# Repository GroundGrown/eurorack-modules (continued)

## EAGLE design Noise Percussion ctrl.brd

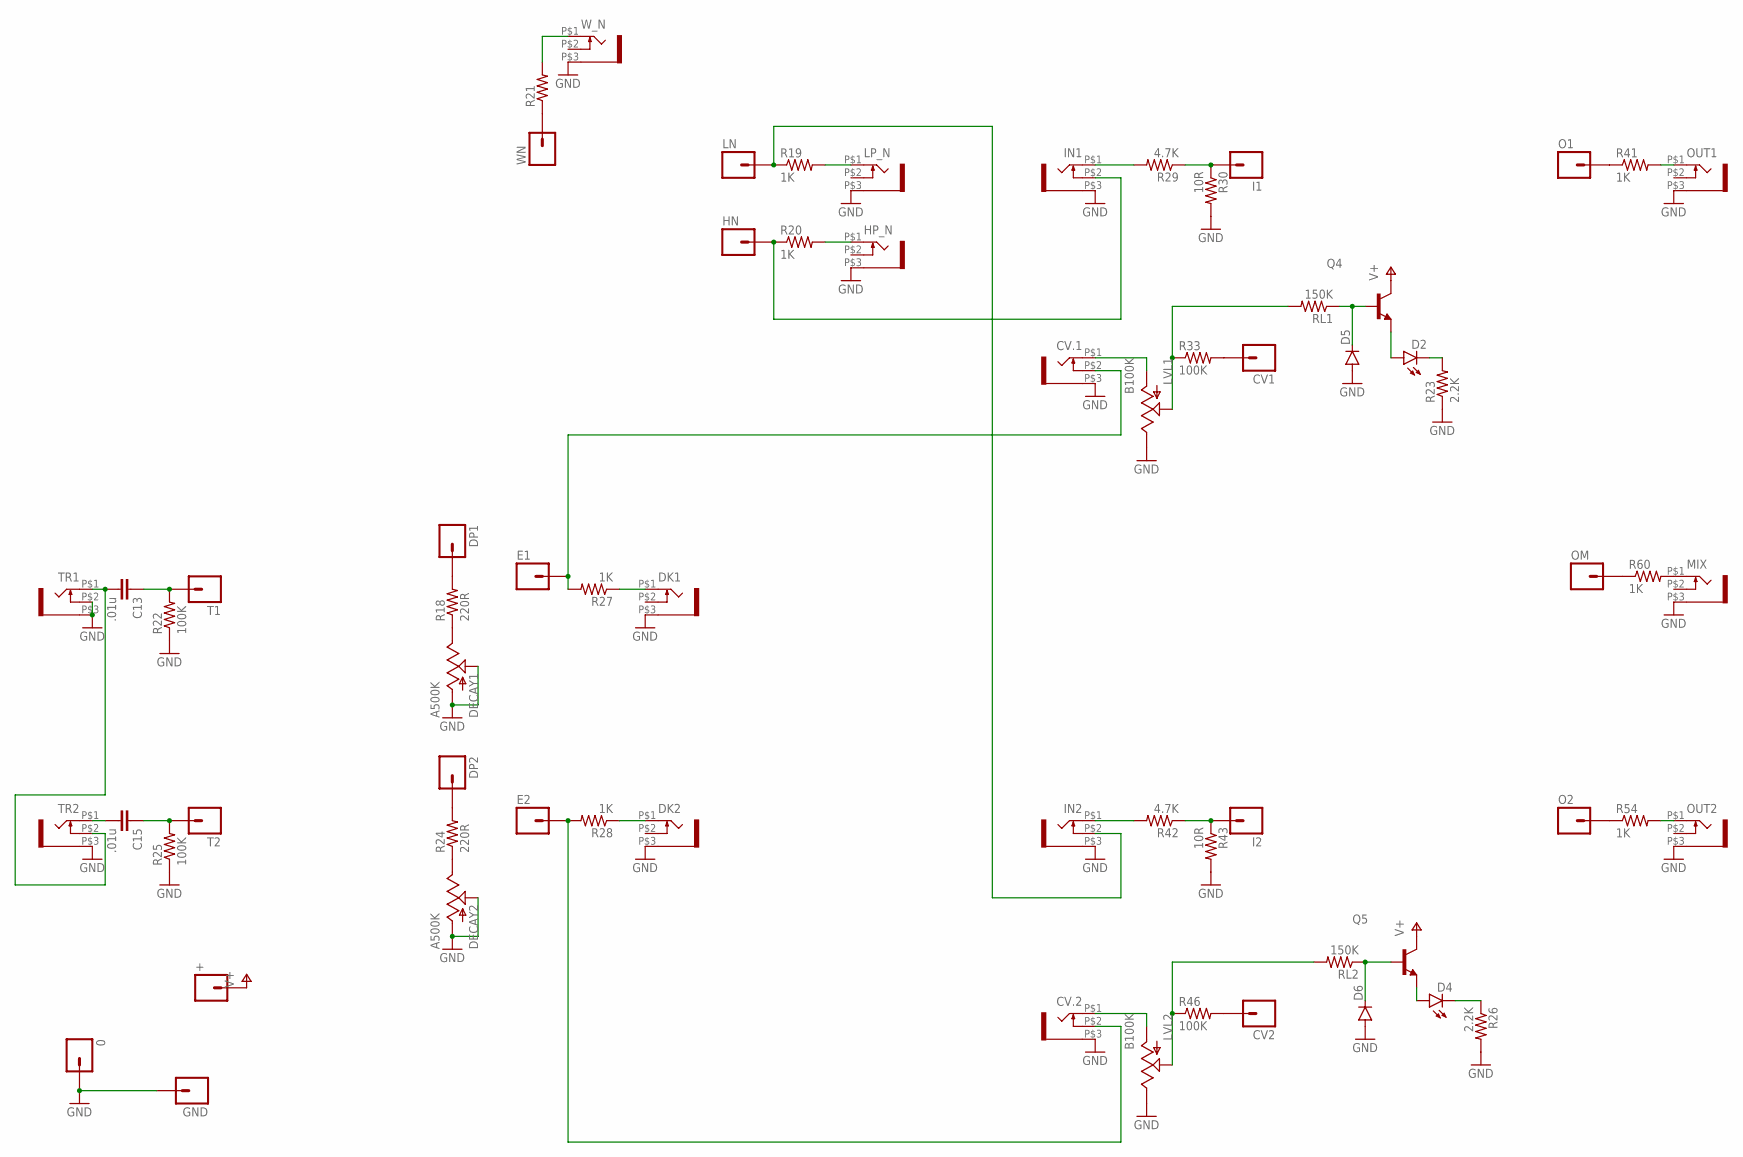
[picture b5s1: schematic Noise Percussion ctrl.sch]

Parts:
0: M01PTH; 1X01
+: M01PTH; 1X01
C13, C15: .01u; 0805
CV1, CV2: M01PTH; 1X01
CV.1, CV.2: WQP-PJ301M-12_JACK
D2, D4: LED3MM
D5, D6: DIODESOD123; SOD-123
DECAY1, DECAY2: A500K; ALPS_POT
DK1, DK2: WQP-PJ301M-12_JACK
DP1, DP2: M01PTH; 1X01
E1, E2: M01PTH; 1X01
GND: M01PTH; 1X01
HN: M01PTH; 1X01
HP_N: WQP-PJ301M-12_JACK
I1, I2: M01PTH; 1X01
IN1, IN2: WQP-PJ301M-12_JACK
LN: M01PTH; 1X01
LP_N: WQP-PJ301M-12_JACK
LVL1, LVL2: B100K; ALPS_POT
MIX: WQP-PJ301M-12_JACK
O1, O2: M01PTH; 1X01
OM: M01PTH; 1X01
OUT1, OUT2: WQP-PJ301M-12_JACK
Q4, Q5: MMBT3904LT1-NPN-SOT23-BEC; SOT23-BEC
R18, R24: 220R; 0805
R19, R20, R27, R28, R41, R54, R60: 1K; 0805
R21: RESISTOR0805-RES; 0805
R22, R25, R33, R46: 100K; 0805
R23, R26: 2.2K; 0805
R29, R42: 4.7K; 0805
R30, R43: 10R; 0805
RL1, RL2: 150K; 0805
T1, T2: M01PTH; 1X01
TR1, TR2: WQP-PJ301M-12_JACK
WN: M01PTH; 1X01
W_N: WQP-PJ301M-12_JACK

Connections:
GND: 0.1, CV.1.P$3 (1), CV.2.P$3 (1), D5.A, D6.A, DECAY1.P$2 (S), DECAY1.P$3 (A), DECAY2.P$2 (S), DECAY2.P$3 (A), DK1.P$3 (1), DK2.P$3 (1), GND.1, HP_N.P$3 (1), IN1.P$3 (1), IN2.P$3 (1), LP_N.P$3 (1), LVL1.P$1 (E), LVL2.P$1 (E), MIX.P$3 (1), OUT1.P$3 (1), OUT2.P$3 (1), R22.1, R23.1, R25.1, R26.2, R30.2, R43.2, TR1.P$2 (3), TR1.P$3 (1), TR2.P$3 (1), W_N.P$3 (1)
unnamed: D6.C, Q5.B, RL2.1
unnamed: HN.1, IN1.P$2 (3), R20.1
unnamed: IN1.P$1 (2), R29.2
unnamed: I1.1, R29.1, R30.1
unnamed: IN2.P$2 (3), LN.1, R19.1
unnamed: D5.C, Q4.B, RL1.1
unnamed: R21.1, WN.1
unnamed: CV.1.P$2 (3), E1.1, R27.2
unnamed: CV.2.P$2 (3), E2.1, R28.2
unnamed: DP1.1, R18.2
unnamed: DP2.1, R24.2
unnamed: O1.1, R41.1
unnamed: OM.1, R60.1
unnamed: DK2.P$1 (2), R28.1
unnamed: O2.1, R54.1
unnamed: CV1.1, R33.2
unnamed: CV2.1, R46.2
unnamed: D2.A, Q4.E
unnamed: D2.K (C), R23.2
unnamed: R21.2, W_N.P$1 (2)
unnamed: LP_N.P$1 (2), R19.2
unnamed: D4.A, Q5.E
unnamed: D4.K (C), R26.1
unnamed: HP_N.P$1 (2), R20.2
unnamed: C13.2, TR1.P$1 (2), TR2.P$2 (3)
unnamed: C13.1, R22.2, T1.1
unnamed: DECAY1.P$1 (E), R18.1
unnamed: C15.2, TR2.P$1 (2)
unnamed: C15.1, R25.2, T2.1
unnamed: DECAY2.P$1 (E), R24.1
unnamed: DK1.P$1 (2), R27.1
unnamed: CV.1.P$1 (2), LVL1.P$3 (A)
unnamed: LVL1.P$2 (S), R33.1, RL1.2
unnamed: OUT1.P$1 (2), R41.2
unnamed: IN2.P$1 (2), R42.2
unnamed: I2.1, R42.1, R43.1
unnamed: CV.2.P$1 (2), LVL2.P$3 (A)
unnamed: LVL2.P$2 (S), R46.1, RL2.2
unnamed: OUT2.P$1 (2), R54.2
unnamed: MIX.P$1 (2), R60.2
V+: +.1, Q4.C, Q5.C

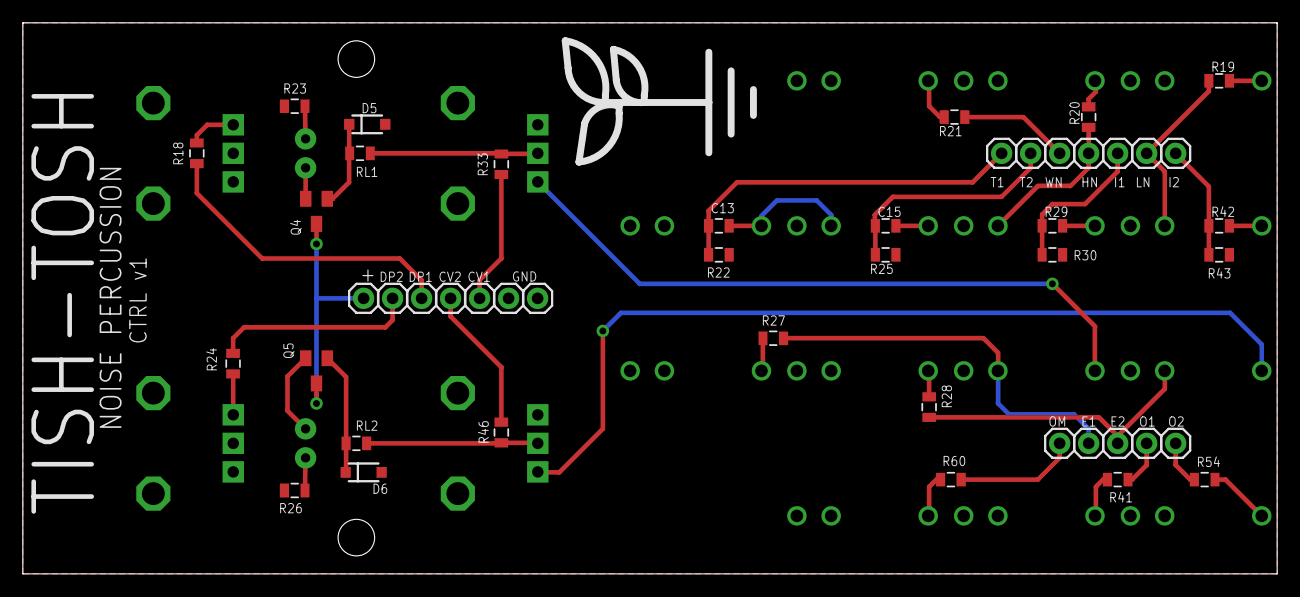
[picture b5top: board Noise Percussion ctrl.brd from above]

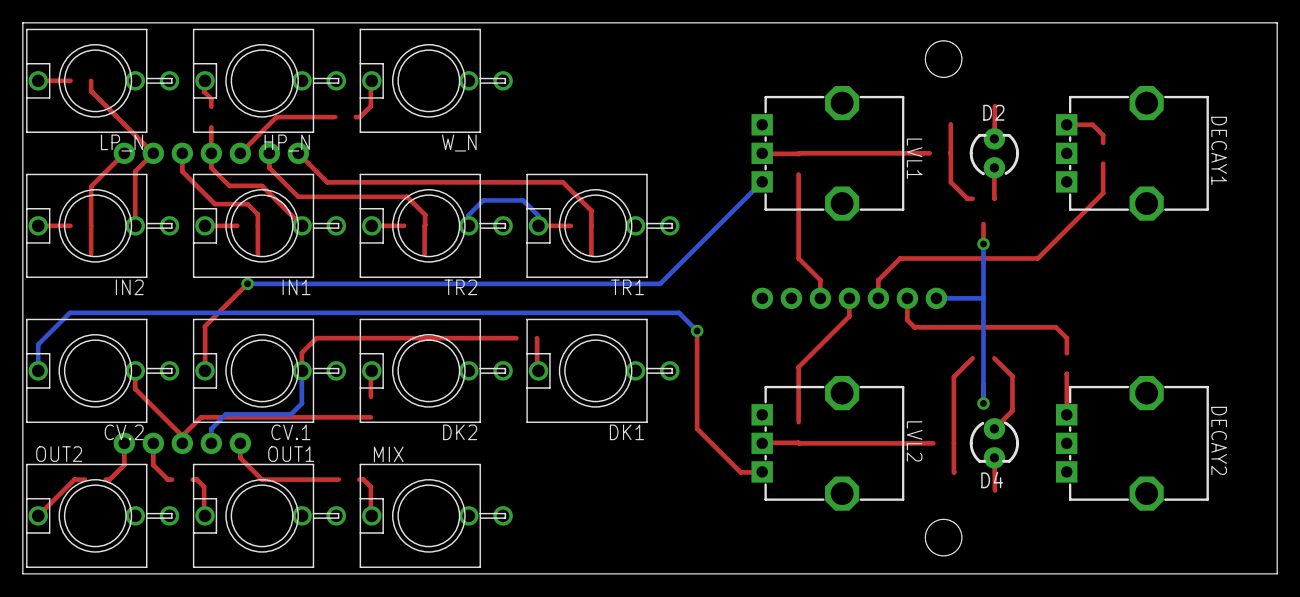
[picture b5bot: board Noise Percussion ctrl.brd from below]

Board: 2 copper layers, 109.9 x 48.3 mm, 68 parts (20 on the bottom side), 42 nets.

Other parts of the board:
U$1: LOGO_LARGE

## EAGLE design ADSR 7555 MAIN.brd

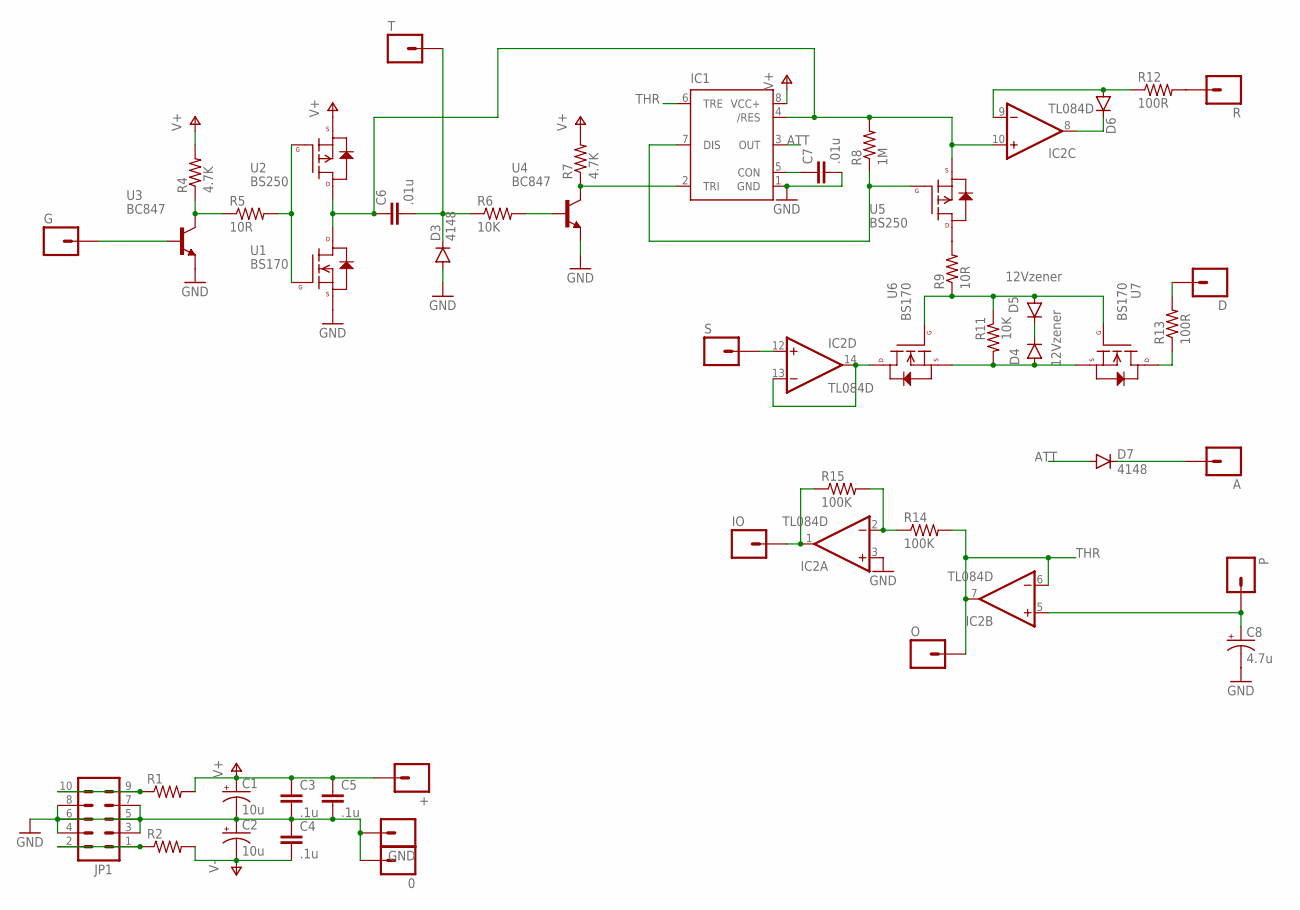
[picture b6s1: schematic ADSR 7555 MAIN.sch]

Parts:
0: M01PTH; 1X01
+: M01PTH; 1X01
A: M01PTH; 1X01
C1, C2: 10u; CPOL-RADIAL-10UF-25V
C3, C4, C5: .1u; 0805
C6, C7: .01u; 0805
C8: 4.7u; CPOL-RADIAL-10UF-25V
D: M01PTH; 1X01
D3, D7: 4148; SOD-123
D4, D5: 12Vzener; SOD-123
D6: DIODESOD123; SOD-123
G: M01PTH; 1X01
GND: M01PTH; 1X01
IC1: NE555D; SO08
IC2: TL084D; SO14
IO: M01PTH; 1X01
JP1: M05X2PTH; AVR_ICSP
O: M01PTH; 1X01
P: M01PTH; 1X01
R: M01PTH; 1X01
R1, R2: RESISTOR0805-RES; 0805@1
R4, R7: 4.7K; 0805@1
R5, R9: 10R; 0805@1
R6, R11: 10K; 0805@1
R8: 1M; 0805@1
R12, R13: 100R; 0805@1
R14, R15: 100K; 0805@1
S: M01PTH; 1X01
T: M01PTH; 1X01
U1, U6, U7: BS170; SOT23-3
U2, U5: BS250; SOT23-3
U3, U4: BC847; SOT23

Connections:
ATT: D7.A, IC1.3 (OUT)
GND: 0.1, C1.2 (-), C2.1 (+), C3.2, C4.1, C5.2, C7.2, C8.2 (-), D3.A, GND.1, IC1.1 (GND), IC2.3 (+IN), JP1.3, JP1.4, JP1.5, JP1.6, JP1.7, JP1.8, U1.2 (S), U3.2 (E), U4.2 (E)
unnamed: JP1.9, JP1.10, R1.1
unnamed: JP1.1, JP1.2, R2.1
unnamed: IC1.2 (TRI), R7.1, U4.3 (C)
unnamed: G.1, U3.1 (B)
unnamed: C8.1 (+), IC2.5 (+IN), P.1
unnamed: R4.1, R5.1, U3.3 (C)
unnamed: C7.1, IC1.5 (CON)
unnamed: R5.2, U1.1 (G), U2.1 (G)
unnamed: C6.1, IC1.4 (/RES), IC2.10 (+IN), R8.2, U1.3 (D), U2.3 (D), U5.2 (S)
unnamed: C6.2, D3.C, R6.1, T.1
unnamed: R6.2, U4.1 (B)
unnamed: R.1, R12.2
unnamed: IC1.7 (DIS), R8.1, U5.1 (G)
unnamed: R9.2, U5.3 (D)
unnamed: D6.A, IC2.9 (-IN), R12.1
unnamed: IC2.12 (+IN), S.1
unnamed: IC2.13 (-IN), IC2.14 (OUT), U6.3 (D)
unnamed: D4.A, R11.2, U6.2 (S), U7.2 (S)
unnamed: D4.C, D5.C
unnamed: D5.A, R9.1, R11.1, U6.1 (G), U7.1 (G)
unnamed: A.1, D7.C
unnamed: D6.C, IC2.8 (OUT)
unnamed: D.1, R13.2
unnamed: R13.1, U7.3 (D)
unnamed: IC2.2 (-IN), R14.1, R15.2
unnamed: IC2.1 (OUT), IO.1, R15.1
THR: IC1.6 (TRE), IC2.6 (-IN), IC2.7 (OUT), O.1, R14.2
V+: +.1, C1.1 (+), C3.1, C5.1, IC1.8 (VCC+), IC2.4 (V+), R1.2, R4.2, R7.2, U2.2 (S)
V-: C2.2 (-), C4.2, IC2.11 (V-), R2.2

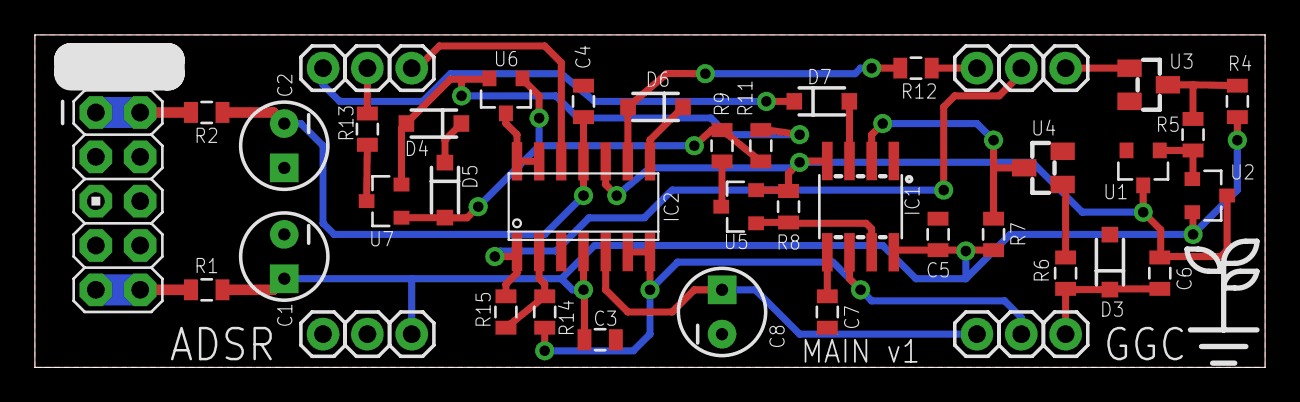
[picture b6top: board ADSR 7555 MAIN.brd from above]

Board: 2 copper layers, 70.5 x 19.1 mm, 49 parts (0 on the bottom side), 31 nets.

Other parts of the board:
U$1: LOGO_SMALL

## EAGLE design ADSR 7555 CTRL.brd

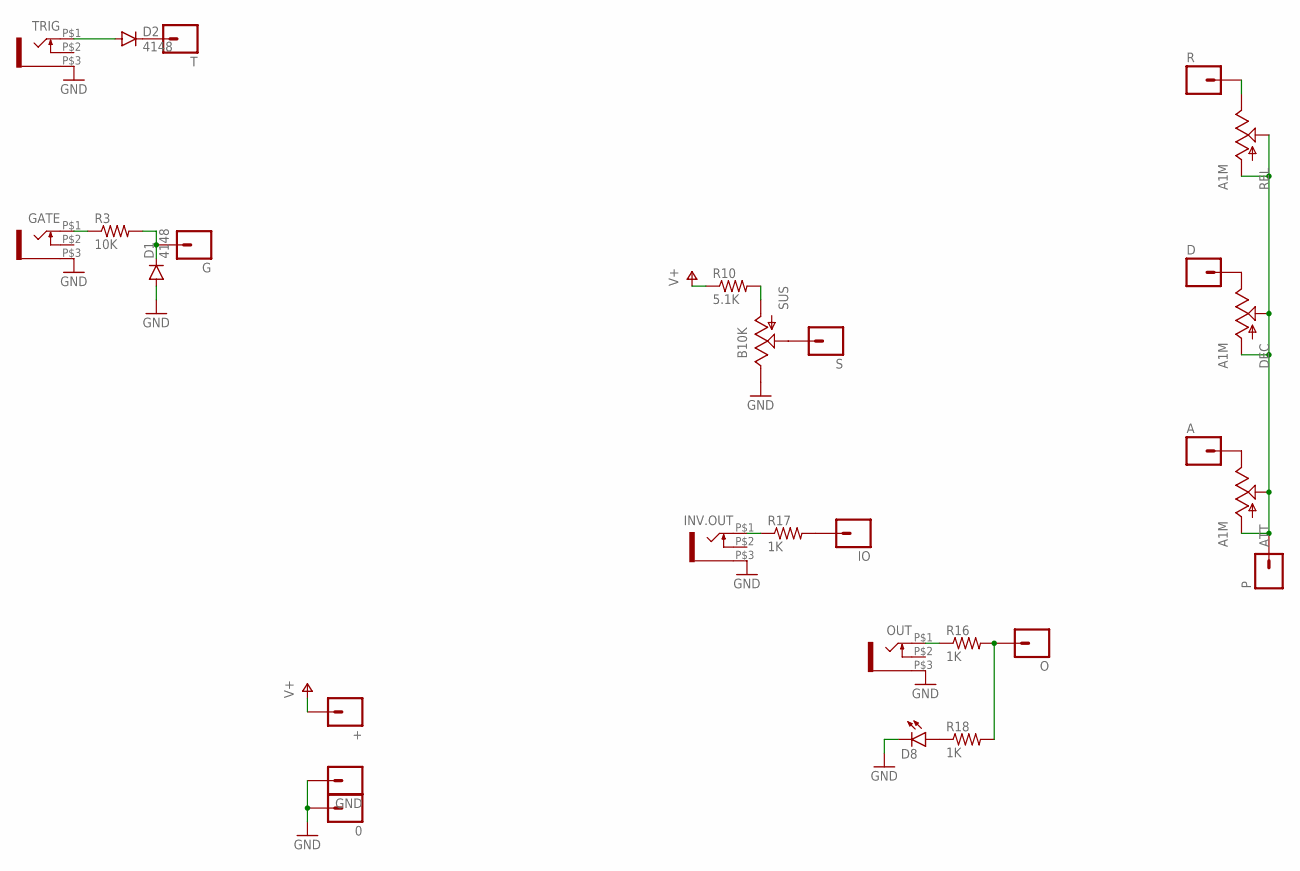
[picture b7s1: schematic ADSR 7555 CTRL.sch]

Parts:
0: M01PTH; 1X01
+: M01PTH; 1X01
A: M01PTH; 1X01
ATT: A1M; ALPS_POT
D: M01PTH; 1X01
D1, D2: 4148; SOD-123
D8: LED3MM
DEC: A1M; ALPS_POT
G: M01PTH; 1X01
GATE: WQP-PJ301M-12_JACK
GND: M01PTH; 1X01
INV.OUT: WQP-PJ301M-12_JACK
IO: M01PTH; 1X01
O: M01PTH; 1X01
OUT: WQP-PJ301M-12_JACK
P: M01PTH; 1X01
R: M01PTH; 1X01
R3: 10K; 0805@1
R10: 5.1K; 0805@1
R16, R17, R18: 1K; 0805@1
REL: A1M; ALPS_POT
S: M01PTH; 1X01
SUS: B10K; ALPS_POT
T: M01PTH; 1X01
TRIG: WQP-PJ301M-12_JACK

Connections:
GND: 0.1, D1.A, D8.K (C), GATE.P$3 (1), GND.1, INV.OUT.P$3 (1), OUT.P$3 (1), SUS.P$1 (E), TRIG.P$3 (1)
unnamed: D2.C, T.1
unnamed: S.1, SUS.P$2 (S)
unnamed: IO.1, R17.2
unnamed: GATE.P$1 (2), R3.1
unnamed: D1.C, G.1, R3.2
unnamed: O.1, R16.2, R18.2
unnamed: A.1, ATT.P$1 (E)
unnamed: D.1, DEC.P$1 (E)
unnamed: D8.A, R18.1
unnamed: D2.A, TRIG.P$1 (2)
unnamed: R10.2, SUS.P$3 (A)
unnamed: R.1, REL.P$1 (E)
unnamed: ATT.P$2 (S), ATT.P$3 (A), DEC.P$2 (S), DEC.P$3 (A), P.1, REL.P$2 (S), REL.P$3 (A)
unnamed: INV.OUT.P$1 (2), R17.1
unnamed: OUT.P$1 (2), R16.1
V+: +.1, R10.1

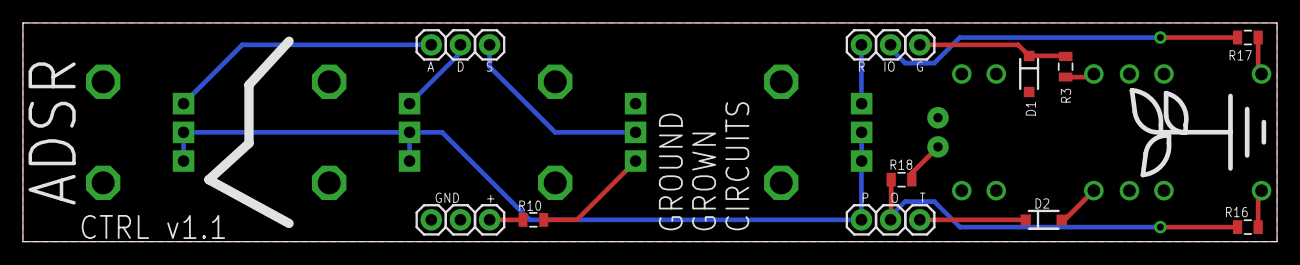
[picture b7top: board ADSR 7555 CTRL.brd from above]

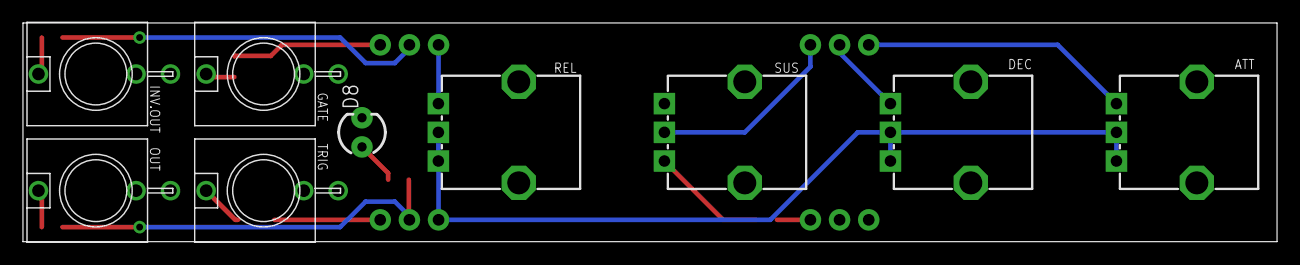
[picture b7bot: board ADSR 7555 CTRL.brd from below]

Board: 2 copper layers, 109.2 x 19.1 mm, 29 parts (9 on the bottom side), 17 nets.

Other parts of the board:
U$1: LOGO_MED

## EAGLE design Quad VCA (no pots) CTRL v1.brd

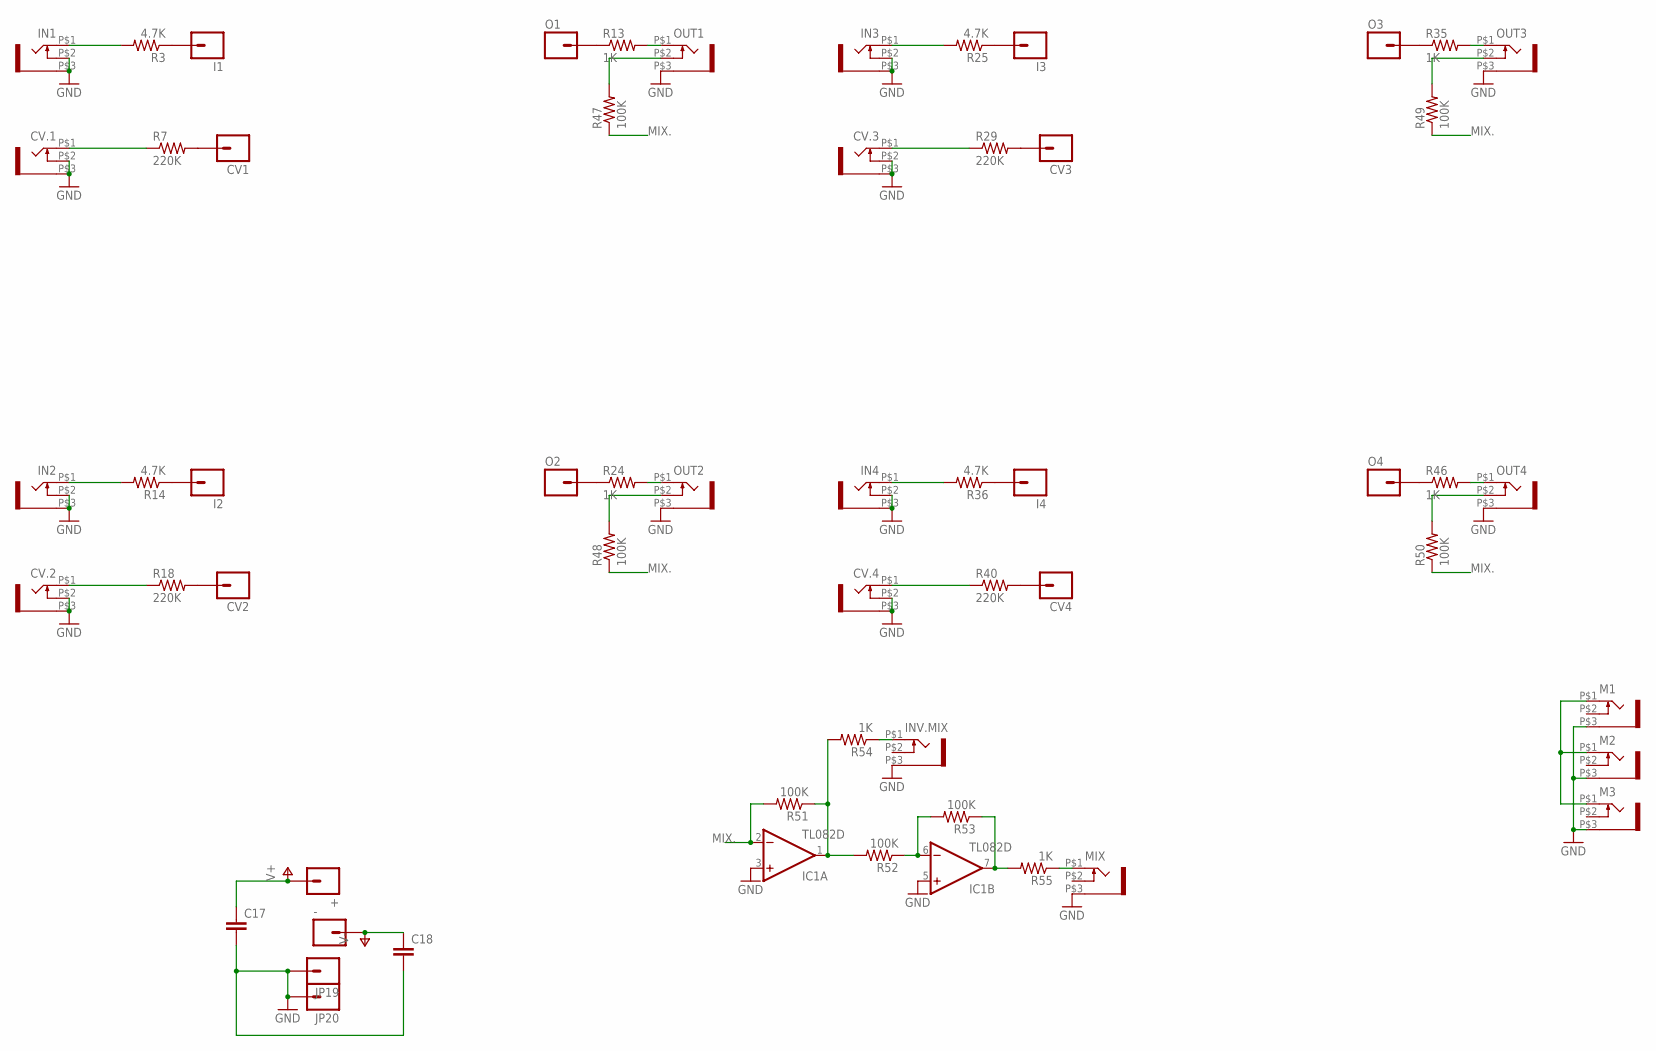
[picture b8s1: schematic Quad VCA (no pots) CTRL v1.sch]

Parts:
+: M01PTH; 1X01
-: M01PTH; 1X01
C17, C18: CAP0805; 0805
CV1, CV2, CV3, CV4: M01PTH; 1X01
CV.1, CV.2, CV.3, CV.4: WQP-PJ301M-12_JACK
I1, I2, I3, I4: M01PTH; 1X01
IC1: TL082D; SO08
IN1, IN2, IN3, IN4: WQP-PJ301M-12_JACK
INV.MIX: WQP-PJ301M-12_JACK
JP19, JP20: M01PTH; 1X01
M1, M2, M3: WQP-PJ301M-12_JACK
MIX: WQP-PJ301M-12_JACK
O1, O2, O3, O4: M01PTH; 1X01
OUT1, OUT2, OUT3, OUT4: WQP-PJ301M-12_JACK
R3, R14, R25, R36: 4.7K; 0805
R7, R18, R29, R40: 220K; 0805
R13, R24, R35, R46, R54, R55: 1K; 0805
R47, R48, R49, R50, R51, R52, R53: 100K; 0805

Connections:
GND: C17.2, C18.2, CV.1.P$2 (3), CV.1.P$3 (1), CV.2.P$2 (3), CV.2.P$3 (1), CV.3.P$2 (3), CV.3.P$3 (1), CV.4.P$2 (3), CV.4.P$3 (1), IC1.3 (+IN), IC1.5 (+IN), IN1.P$2 (3), IN1.P$3 (1), IN2.P$2 (3), IN2.P$3 (1), IN3.P$2 (3), IN3.P$3 (1), IN4.P$2 (3), IN4.P$3 (1), INV.MIX.P$3 (1), JP19.1, JP20.1, M1.P$3 (1), M2.P$3 (1), M3.P$3 (1), MIX.P$3 (1), OUT1.P$3 (1), OUT2.P$3 (1), OUT3.P$3 (1), OUT4.P$3 (1)
MIX.: IC1.2 (-IN), R47.1, R48.1, R49.1, R50.1, R51.2
unnamed: M1.P$1 (2), M2.P$1 (2), M3.P$1 (2)
unnamed: I1.1, R3.1
unnamed: IN1.P$1 (2), R3.2
unnamed: CV1.1, R7.2
unnamed: O1.1, R13.1
unnamed: CV.2.P$1 (2), R18.1
unnamed: IC1.1 (OUT), R51.1, R52.2, R54.2
unnamed: IC1.6 (-IN), R52.1, R53.2
unnamed: OUT1.P$2 (3), R47.2
unnamed: IN2.P$1 (2), R14.2
unnamed: I2.1, R14.1
unnamed: O2.1, R24.1
unnamed: O3.1, R35.1
unnamed: O4.1, R46.1
unnamed: CV4.1, R40.2
unnamed: I4.1, R36.1
unnamed: CV3.1, R29.2
unnamed: IC1.7 (OUT), R53.1, R55.2
unnamed: CV.1.P$1 (2), R7.1
unnamed: I3.1, R25.1
unnamed: CV2.1, R18.2
unnamed: INV.MIX.P$1 (2), R54.1
unnamed: MIX.P$1 (2), R55.1
unnamed: OUT2.P$1 (2), R24.2
unnamed: IN3.P$1 (2), R25.2
unnamed: CV.3.P$1 (2), R29.1
unnamed: CV.4.P$1 (2), R40.1
unnamed: OUT1.P$1 (2), R13.2
unnamed: OUT3.P$1 (2), R35.2
unnamed: IN4.P$1 (2), R36.2
unnamed: OUT2.P$2 (3), R48.2
unnamed: OUT4.P$1 (2), R46.2
unnamed: OUT3.P$2 (3), R49.2
unnamed: OUT4.P$2 (3), R50.2
V+: +.1, C17.1, IC1.8 (V+)
V-: -.1, C18.1, IC1.4 (V-)

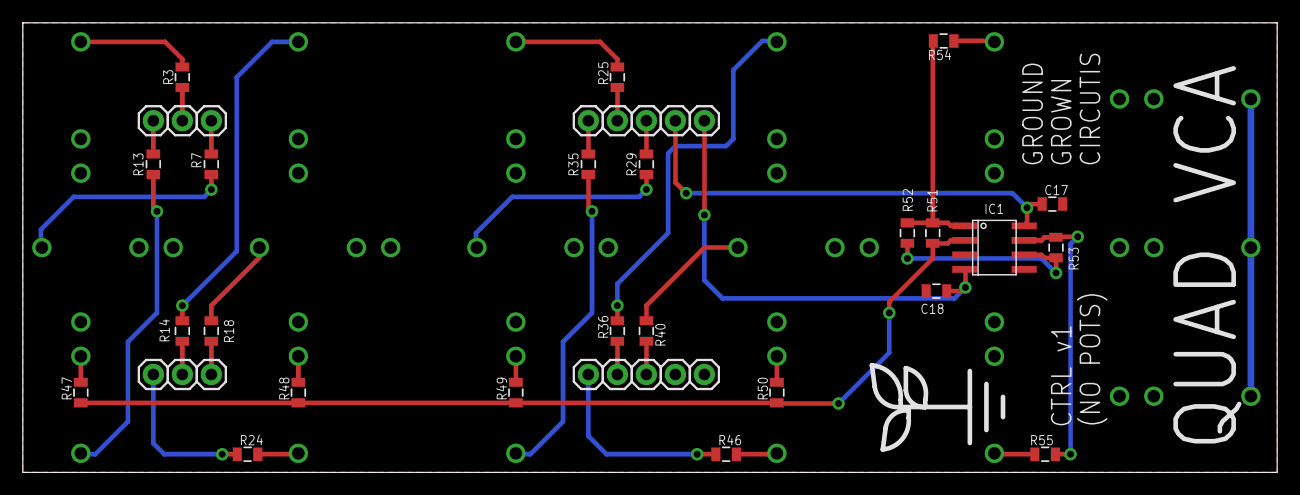
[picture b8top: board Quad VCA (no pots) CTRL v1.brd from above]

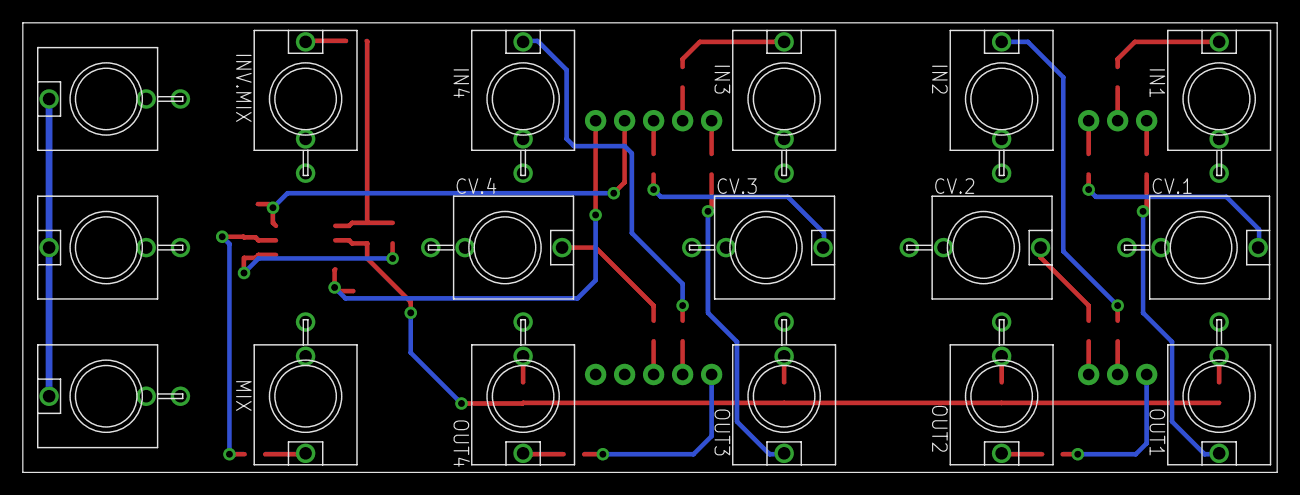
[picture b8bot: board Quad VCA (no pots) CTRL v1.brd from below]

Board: 2 copper layers, 109.9 x 39.4 mm, 58 parts (17 on the bottom side), 38 nets.

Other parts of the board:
U$1: LOGO_MED
